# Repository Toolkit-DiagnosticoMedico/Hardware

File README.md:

# Hardware
Diseño de un Sistema Modular que permitirá medir magnitudes físicas relacionadas a la salud del paciente con la finalidad de
“subirlos la nube” para acceso de diversos servicios. Los parámetros a medir que se manejarán en ésta primera versión serán 
la temperatura, el pulso cardiaco, la presión arterial y la cantidad de la glucosa en la sangre.

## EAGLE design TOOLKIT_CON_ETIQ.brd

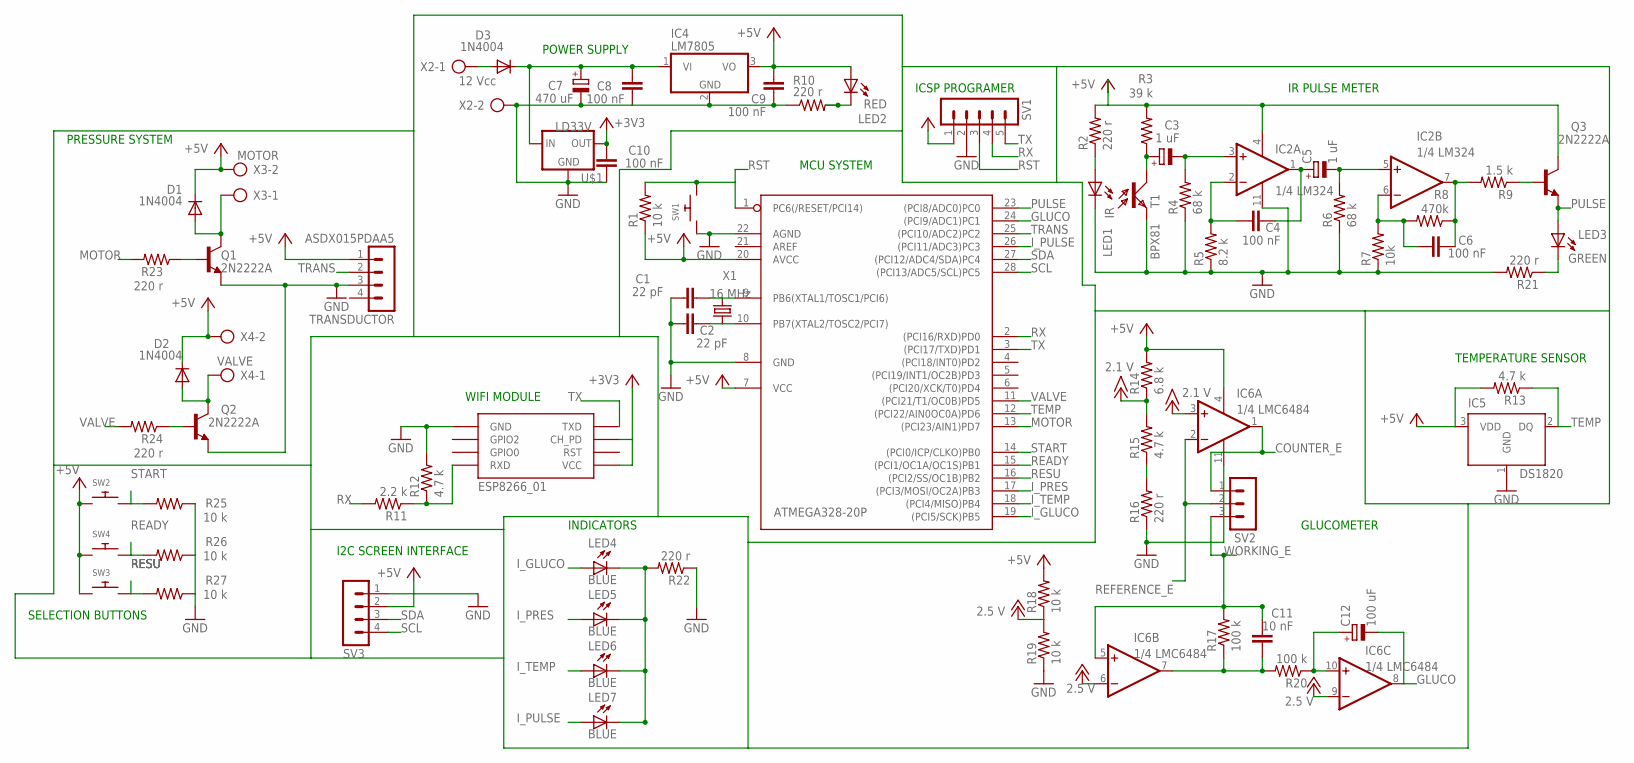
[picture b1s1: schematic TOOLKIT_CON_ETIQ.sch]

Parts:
C1, C2: 22 pF; C050-024X044
C3, C5: 1 uF; E2,5-6E
C4, C6, C8, C9, C10: 100 nF; C050-025X075
C7: 470 uF; E2,5-6E
C11: 10 nF; C050-025X075
C12: 100 uF; E2,5-6E
D1, D2, D3: 1N4004; DO41-10
IC1: ATMEGA328-20P; DIL28-3
IC2: 1/4 LM324; DIL14
IC4: LM7805; TO220V
IC5: DS1820; TO-92
IC6: 1/4 LMC6484; DIL14
LED1: IR; LED3MM
LED2: RED; LED3MM
LED3: GREEN; LED3MM
LED4, LED5, LED6, LED7: BLUE; LED3MM
Q1, Q2, Q3: 2N2222A; TO92-EBC
R1, R18, R19, R25, R26, R27: 10 k; 0207/10
R2, R10, R16, R21, R22, R23, R24: 220 r; 0207/10
R3: 39 k; 0207/10
R4, R6: 68 k; 0207/10
R5: 8.2 k; 0207/10
R7: 10k; 0207/10
R8: 470k; 0207/10
R9: 1.5 k; 0207/10
R11: 2.2 k; 0207/10
R12, R13, R15: 4.7 k; 0207/10
R14: 6.8 k; 0207/10
R17, R20: 100 k; 0207/10
SV1: MA05-1
SV2: MA03-1
SV3: MA04-1
SW1, SW2, SW3, SW4: SWITCH_PUSHBUTTONEVQ-PE; TACT_PANA-EVQ
T1: BPX81
TRANSDUCTOR: ASDX015PDAA5; MA04-1
U$1: LD33V; LD1117V33
U$2: ESP8266_01; ESP01
X1: 16 MHz; HC18U-V
X2: 12 Vcc; AK500/2
X3: MOTOR; AK500/2
X4: VALVE; AK500/2

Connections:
+3V3: C10.2, U$1.OUT, U$2.CH_PD, U$2.VCC
+12V: IC6.6 (-IN), IC6.9 (-IN), R18.1, R19.2
+15V: IC6.3 (+IN), R14.1, R15.2
COUNTER_E: IC6.1 (OUT), SV2.1
GLUCO: C12.-, IC1.24 ((PCI9/ADC1)PC1), IC6.8 (OUT)
GND: C1.1, C2.1, C7.-, C8.1, C9.1, C10.1, IC1.8 (GND), IC1.22 (AGND), IC2.11 (V-), IC4.2 (GND), IC5.1 (GND), IC6.11 (V-), LED1.K (C), Q1.E, Q2.E, R4.1, R5.1, R6.1, R7.1, R10.1, R12.2, R16.1, R19.1, R21.2, R22.1, R25.1, R26.1, R27.1, SV1.2, SV3.1, SW1.P$1, T1.E, TRANSDUCTOR.3, U$1.GND, U$2.GND, X2.2
I_GLUCO: IC1.19 ((PCI5/SCK)PB5), LED4.A
I_PRES: IC1.17 ((PCI3/MOSI/OC2A)PB3), LED5.A
I_PULSE: IC1.26 ((PCI11/ADC3)PC3), LED7.A
I_TEMP: IC1.18 ((PCI4/MISO)PB4), LED6.A
MOTOR: IC1.13 ((PCI23/AIN1)PD7), R23.2
unnamed: C1.2, IC1.9 (PB6(XTAL1/TOSC1/PCI6)), X1.1
unnamed: C2.2, IC1.10 (PB7(XTAL2/TOSC2/PCI7)), X1.2
unnamed: R11.1, R12.1, U$2.RX (RXD)
unnamed: LED1.A, R2.1
unnamed: C3.+, R3.1, T1.C
unnamed: C3.-, IC2.3 (+IN), R4.2
unnamed: C4.1, IC2.2 (-IN), R5.2
unnamed: C6.1, IC2.6 (-IN), R7.2, R8.2
unnamed: C6.2, IC2.7 (OUT), R8.1, R9.2
unnamed: C4.2, C5.+, IC2.1 (OUT)
unnamed: C5.-, IC2.5 (+IN), R6.2
unnamed: Q3.B, R9.1
unnamed: R15.1, R16.2
unnamed: LED3.K (C), R21.1
unnamed: C7.+, C8.2, D3.C, IC4.1 (VI), U$1.IN
unnamed: LED2.K (C), R10.2
unnamed: LED4.K (C), LED5.K (C), LED6.K (C), LED7.K (C), R22.2
unnamed: C11.1, IC6.7 (OUT), R17.1, R20.2
unnamed: Q1.B, R23.1
unnamed: C12.+, IC6.10 (+IN), R20.1
unnamed: D2.A, Q2.C, X4.1
unnamed: D1.A, Q1.C, X3.1
unnamed: Q2.B, R24.1
unnamed: D3.A, X2.1
PULSE: IC1.23 ((PCI8/ADC0)PC0), LED3.A, Q3.E
READY: IC1.15 ((PCI1/OC1A/OC1S)PB1), R26.2, SW4.P$2
REFERENCE_E: IC6.2 (-IN), SV2.2
RESU: IC1.16 ((PCI2/SS/OC1B)PB2), R27.2, SW3.P$2
RST: IC1.1 (PC6(/RESET/PCI14)), R1.2, SV1.3, SW1.P$2
RX: IC1.2 ((PCI16/RXD)PD0), R11.2, SV1.4
SCL: IC1.28 ((PCI13/ADC5/SCL)PC5), SV3.4
SDA: IC1.27 ((PCI12/ADC4/SDA)PC4), SV3.3
START: IC1.14 ((PCI0/ICP/CLKO)PB0), R25.2, SW2.P$2
TEMP: IC1.12 ((PCI22/AIN0OC0A)PD6), IC5.2 (DQ), R13.1
TRANS: IC1.25 ((PCI10/ADC2)PC2), TRANSDUCTOR.2
TX: IC1.3 ((PCI17/TXD)PD1), SV1.5, U$2.TX (TXD)
VALVE: IC1.11 ((PCI21/T1/OC0B)PD5), R24.2
WORKING_E: C11.2, IC6.5 (+IN), R17.2, SV2.3

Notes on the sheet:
POWER SUPPLY
WIFI MODULE
I2C SCREEN INTERFACE
IR PULSE METER
TEMPERATURE SENSOR
GLUCOMETER
ICSP PROGRAMER
INDICATORS
PRESSURE SYSTEM
MCU SYSTEM
SELECTION BUTTONS

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
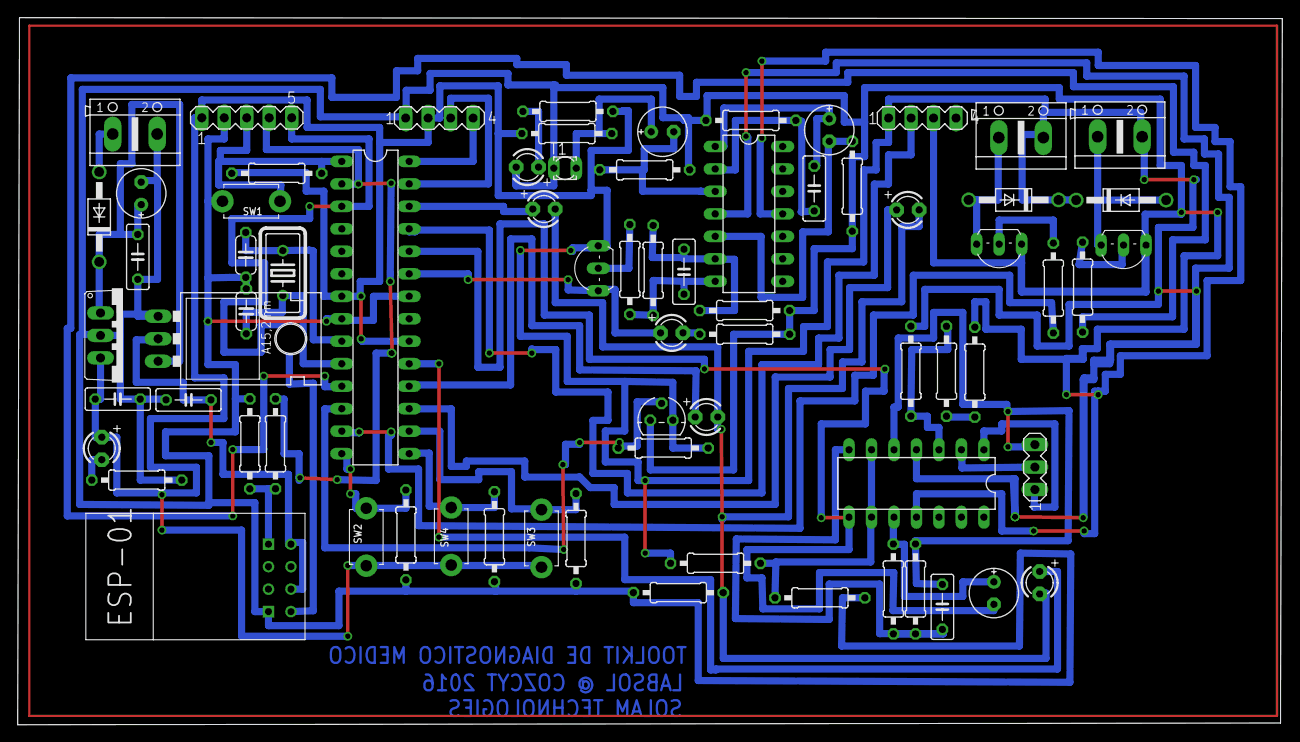
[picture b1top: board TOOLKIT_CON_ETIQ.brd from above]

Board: 2 copper layers, 142.9 x 79.9 mm, 72 parts (0 on the bottom side), 51 nets.

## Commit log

2016-10-24 Esquema de la conexión de sensores del Toolkit
    Sujeto a cambios...
